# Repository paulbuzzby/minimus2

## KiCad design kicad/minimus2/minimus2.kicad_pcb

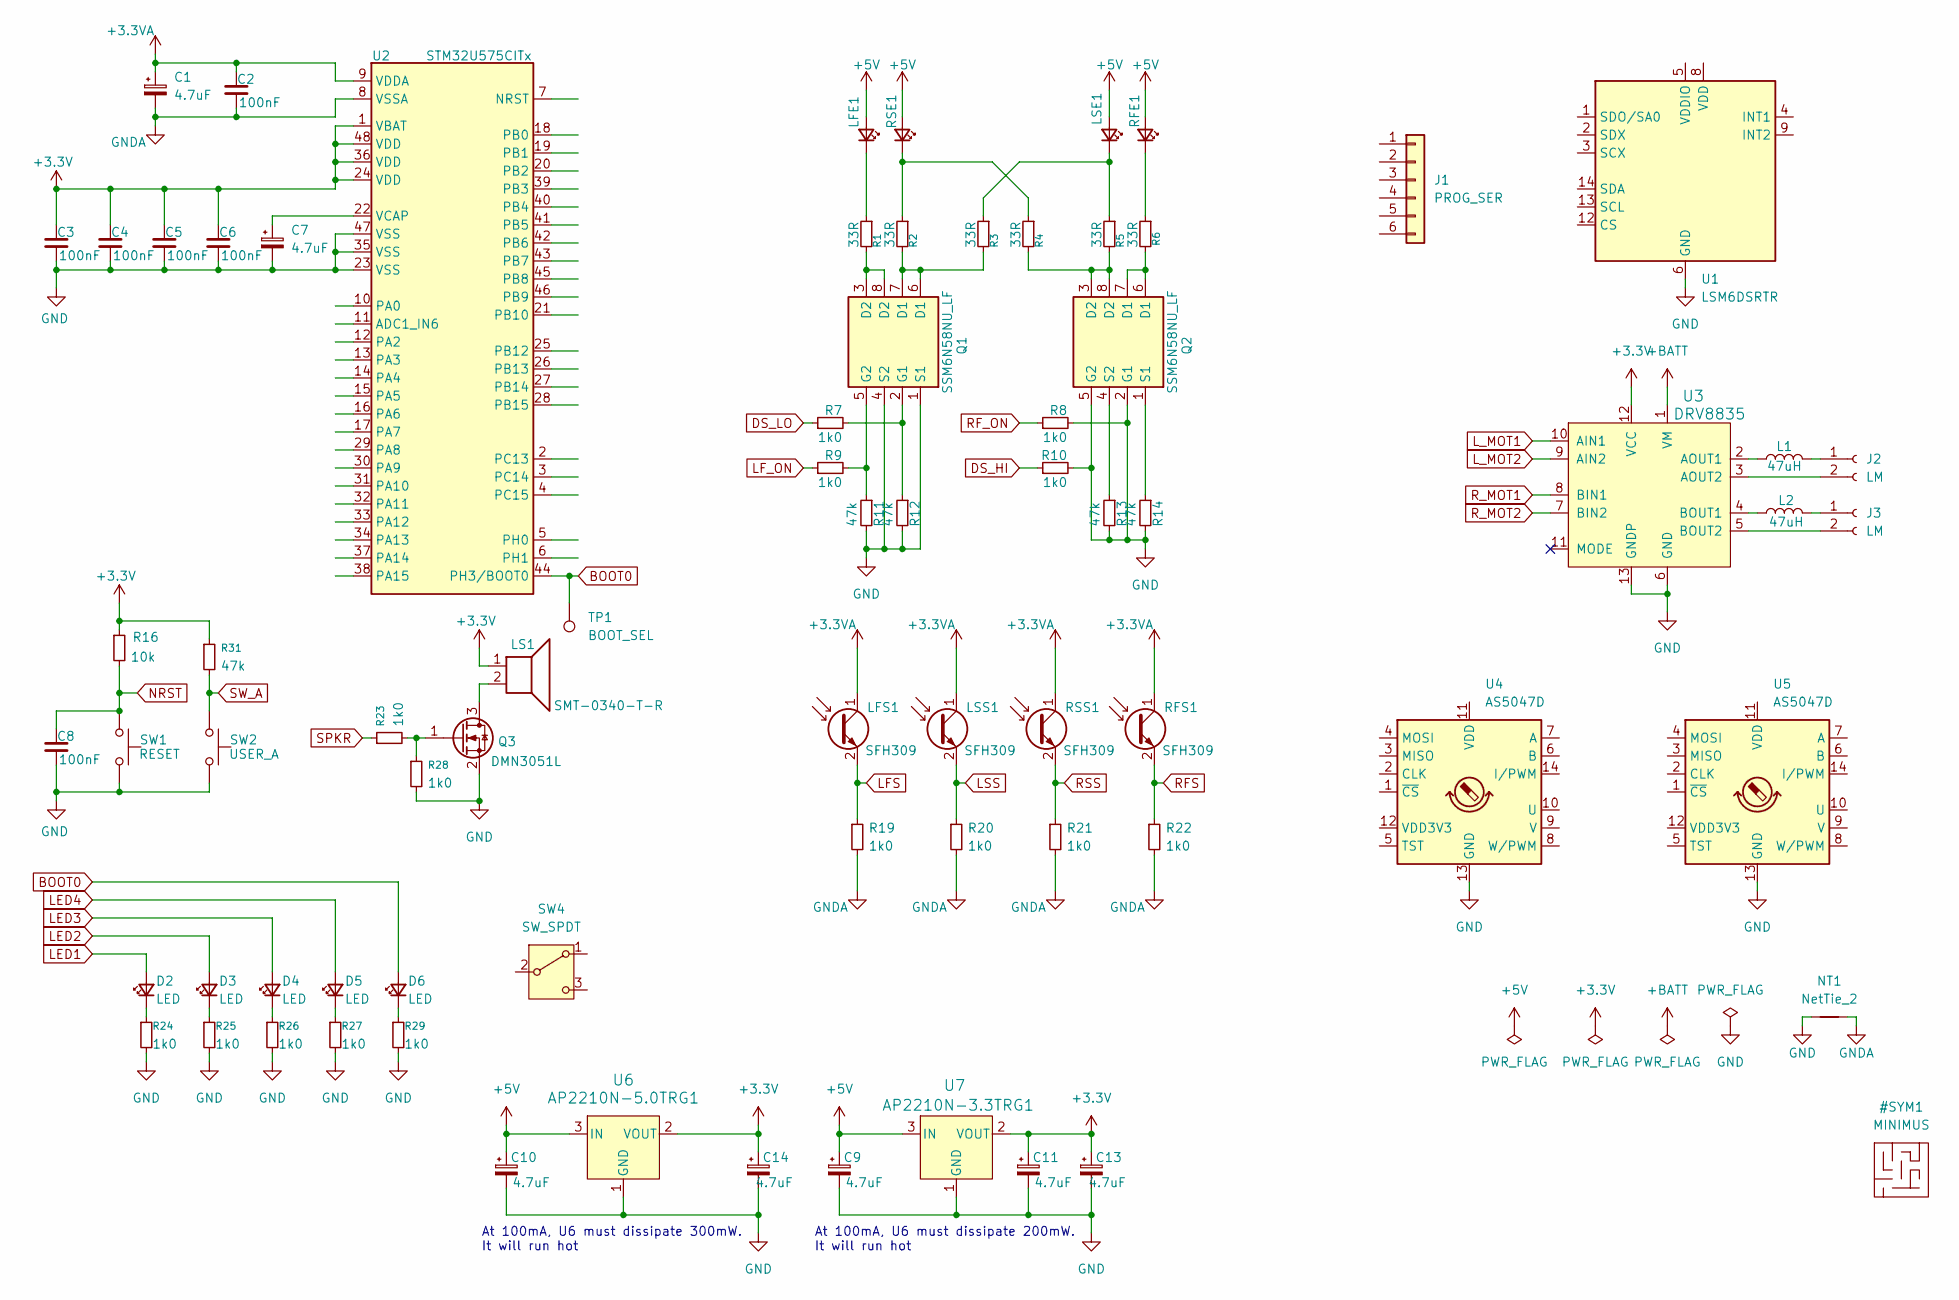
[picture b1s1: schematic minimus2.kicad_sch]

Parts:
C1, C7, C9, C10, C11, C13, C14: 4.7uF; C_0805_2012Metric
C2, C3, C4, C5, C6, C8: 100nF; C_0402_1005Metric
D2, D3, D4, D5, D6: LED; LED_0402_1005Metric
J1: PROG_SER; PinHeader_2x03_P1.27mm_Vertical
J2, J3: LM; PinHeader_1x02_P2.00mm_Vertical
L1, L2: 47uH; IFSC-1515AH-01
LFE1: SFH4050; LED_D3.0mm_Horizontal_O1.27mm_Z2.0mm_IRBlack
LFS1: SFH309; LED_D3.0mm_Horizontal_O1.27mm_Z2.0mm_Clear
LS1: SMT-0340-T-R; LCSC C3811754
LSE1: SFH4050; LED_D3.0mm_Horizontal_O1.27mm_Z2.0mm_IRBlack
LSS1: SFH309; LED_D3.0mm_Horizontal_O1.27mm_Z2.0mm_Clear
NT1: NetTie_2; NetTie-2_SMD_Pad0.5mm
Q1, Q2: SSM6N58NU_LF; SON65P200X200X80-8N
Q3: DMN3051L; SOT-23; LCSC C155348
R1, R2, R3, R4, R5, R6: 33R; R_0402_1005Metric
R7, R8, R9, R10, R19, R20, R21, R22, R23, R24, R25, R26, R27, R28, R29: 1k0; R_0402_1005Metric
R11, R12, R13, R14, R31: 47k; R_0402_1005Metric
R16: 10k; R_0402_1005Metric
RFE1: SFH4050; LED_D3.0mm_Horizontal_O1.27mm_Z2.0mm_IRBlack
RFS1: SFH309; LED_D3.0mm_Horizontal_O1.27mm_Z2.0mm_Clear
RSE1: SFH4050; LED_D3.0mm_Horizontal_O1.27mm_Z2.0mm_IRBlack
RSS1: SFH309; LED_D3.0mm_Horizontal_O1.27mm_Z2.0mm_Clear
SW1: RESET; SW_Push_1P1T_NO_CK_KMR2
SW2: USER_A; SW_Push_1P1T_NO_CK_KMR2
SW4: SW_SPDT; CUS-12TB_NDC
TP1: BOOT_SEL; TestPoint_Pad_D1.0mm
U1: LSM6DSRTR; LGA-14_3x2.5mm_P0.5mm_LayoutBorder3x4y; LCSC C784817
U2: STM32U575CITx; LQFP-48_7x7mm_P0.5mm
U3: DRV8835; LCSC C2848981
U4, U5: AS5047D; TSSOP-14_4.4x5mm_P0.65mm
U6: AP2210N-5.0TRG1; AP2210N-x.xTRG1_DIO
U7: AP2210N-3.3TRG1; AP2210N-x.xTRG1_DIO

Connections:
+3.3V: C3.1, C4.1, C5.1, C6.1, C11.1, C13.1, C14.1, LS1.1, R16.1, R31.1, U2.1 (VBAT), U2.24 (VDD), U2.36 (VDD), U2.48 (VDD), U3.12 (VCC), U6.2 (VOUT), U7.2 (VOUT)
+3.3VA: C1.1, C2.1, LFS1.1 (C), LSS1.1 (C), RFS1.1 (C), RSS1.1 (C), U2.9 (VDDA)
+5V: C9.1, C10.1, LFE1.2 (A), LSE1.2 (A), RFE1.2 (A), RSE1.2 (A), U6.3 (IN), U7.3 (IN)
+BATT: U3.1 (VM)
BOOT0: D6.2 (A), TP1.1, U2.44 (PH3/BOOT0)
DS_HI: R10.1
DS_LO: R7.1
GND: C3.2, C4.2, C5.2, C6.2, C7.2, C8.2, C9.2, C10.2, C11.2, C13.2, C14.2, NT1.1, Q1.1 (S1), Q1.4 (S2), Q2.2 (G1), Q2.5 (G2), Q3.2 (S), R8.2, R10.2, R11.2, R12.2, R13.2, R14.2, R24.2, R25.2, R26.2, R27.2, R28.2, R29.2, SW1.1, SW2.1, U1.6 (GND), U1.7 (GND), U2.23 (VSS), U2.35 (VSS), U2.47 (VSS), U3.6 (GND), U3.13 (GNDP), U4.13 (GND), U5.13 (GND), U6.1 (GND), U7.1 (GND)
GNDA: C1.2, C2.2, NT1.2, R19.2, R20.2, R21.2, R22.2, U2.8 (VSSA)
LED1: D2.2 (A)
LED2: D3.2 (A)
LED3: D4.2 (A)
LED4: D5.2 (A)
LFS: LFS1.2 (E), R19.1
LF_ON: R9.1
LSS: LSS1.2 (E), R20.1
L_MOT1: U3.10 (AIN1)
L_MOT2: U3.9 (AIN2)
NRST: C8.1, R16.2, SW1.2
unnamed: D2.1 (K), R24.1
unnamed: D3.1 (K), R25.1
unnamed: D4.1 (K), R26.1
unnamed: D5.1 (K), R27.1
unnamed: D6.1 (K), R29.1
unnamed: J2.1, L1.2
unnamed: J2.2, U3.3 (AOUT2)
unnamed: J3.1, L2.2
unnamed: J3.2, U3.5 (BOUT2)
unnamed: LFE1.1 (K), R1.1
unnamed: LSE1.1 (K), R3.1, R5.1
unnamed: Q1.6 (D1), Q1.7 (D1), R2.2, R3.2
unnamed: Q1.3 (D2), Q1.8 (D2), R1.2
unnamed: Q1.2 (G1), R7.2, R12.1
unnamed: Q1.5 (G2), R9.2, R11.1
unnamed: Q2.6 (D1), Q2.7 (D1), R6.2
unnamed: Q2.3 (D2), Q2.8 (D2), R4.2, R5.2
unnamed: Q2.1 (S1), R14.1
unnamed: Q2.4 (S2), R13.1
unnamed: LS1.2, Q3.3 (D)
unnamed: Q3.1 (G), R23.2, R28.1
unnamed: R6.1, RFE1.1 (K)
unnamed: R2.1, R4.1, RSE1.1 (K)
unnamed: C7.1, U2.22 (VCAP)
unnamed: L1.1, U3.2 (AOUT1)
unnamed: L2.1, U3.4 (BOUT1)
RFS: R22.1, RFS1.2 (E)
RF_ON: R8.1
RSS: R21.1, RSS1.2 (E)
R_MOT1: U3.8 (BIN1)
R_MOT2: U3.7 (BIN2)
SPKR: R23.1
SW_A: R31.2, SW2.2

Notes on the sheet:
At 100mA, U6 must dissipate 200mW. It will run hot
At 100mA, U6 must dissipate 300mW. It will run hot

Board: 2 copper layers, 74 parts (0 on the bottom side), 38 nets, no tracks yet.

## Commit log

2025-11-04 add encoder datasheets and summary
2025-11-04 add RP2040 Connect schematics for reference
2025-11-04 add BCR420 datasheet
2025-11-05 reorganise the datasheets
2025-11-05 add some encoder making notes
2025-11-06 rename file
2025-11-06 add AL5801 led driver
2025-11-07 update STM32F413 UQFPN48 pins
2025-11-07 update STM32F413 pins
2025-11-07 Add DC-DC converter datasheet
2025-11-07 update pin alternate function tables
2025-11-07 start some encoder notes
2025-11-08 update ADC pins
2025-11-11 adds AW9523 datasheet
2025-11-12 add WeAct STM32U585 docs
2025-11-12 update pin functions for STM32U585
2025-11-14 add some magnet suppliers
2025-11-18 add dnano parts list
2025-11-20 swap out the imu datasheet
2025-11-20 add some sensor datasheets
2025-11-20 add a steering sim spreadsheet from kojima(?)
2025-11-20 add kerise libraries for kiad
2025-11-20 start adding parts to schematic
2025-11-23 add datasheets
2025-11-23 add libraries
2025-11-23 update kiad files
2025-11-25 add dual mosfet datasheet
2025-11-25 Rough place most parts
2025-11-26 add some parts libraries
2025-11-26 add a mosfet datasheet
2025-11-26 add 3D model for BCR420UFD
2025-11-26 neaten up the buttons
2025-11-26 rename the sensor emitter nets
2025-11-26 pcb update
2025-11-26 remove unused switch and sensor
2025-11-26 add some regulator datasheets
2025-11-26 add AP2210 regulator library entries
2025-11-26 remove library downloads
2025-11-26 add regulators and rotate board
2025-11-27 add power switch library
2025-11-27 add speaker model
2025-11-27 update libraries
2025-11-27 add io expander datasheet
2025-11-27 update gitignore
2025-11-27 update board footprints
2025-11-27 Added notes about wheel assembly process
